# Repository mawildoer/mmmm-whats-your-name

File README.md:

# mmmm-whats-your-name

This is a simple LED matrix, with boost converters to run from a single-cell LiPo.

It's based on an RP2040 and SK6805 LEDs.

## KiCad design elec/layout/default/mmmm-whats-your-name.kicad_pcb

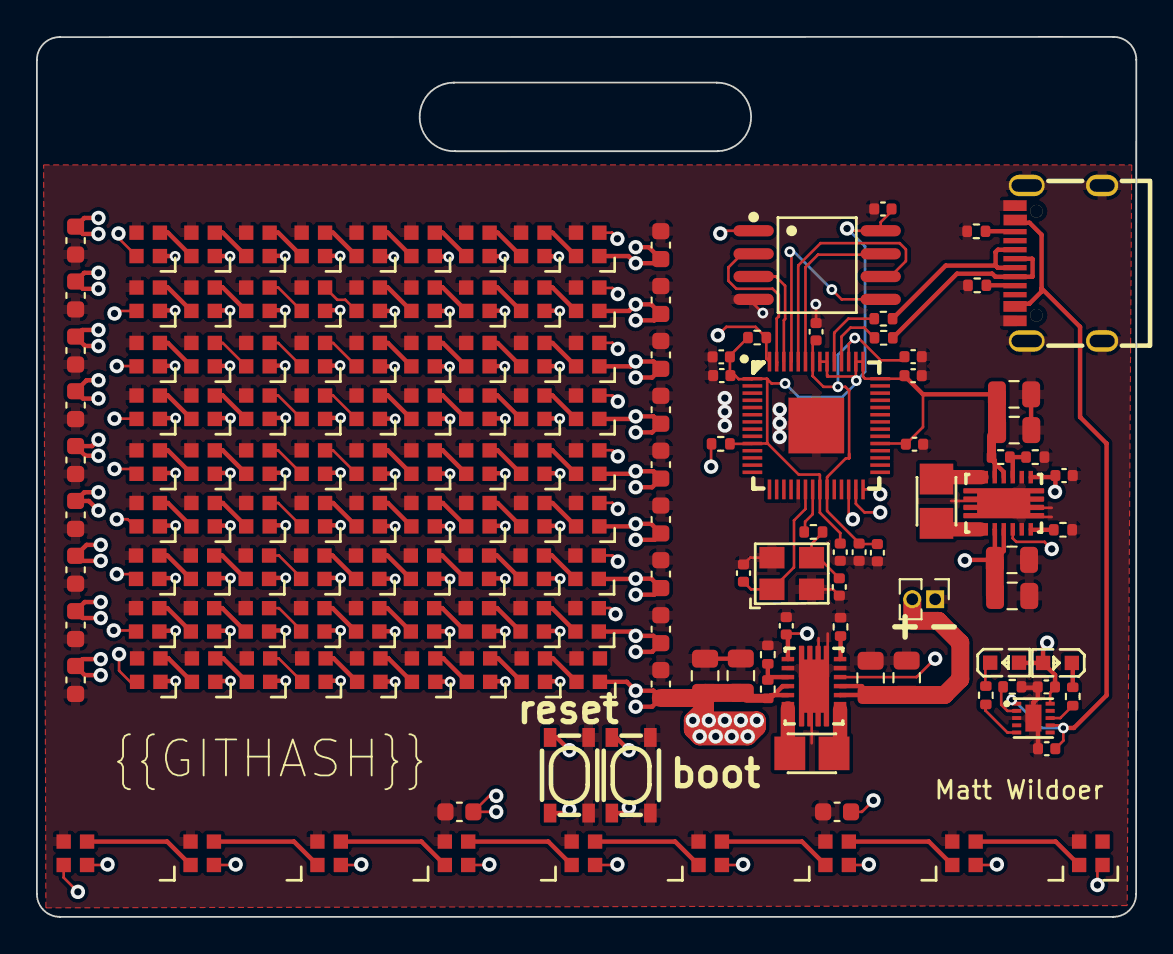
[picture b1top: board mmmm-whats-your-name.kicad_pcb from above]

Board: 4 copper layers, 61.1 x 48.9 mm, 164 parts (0 on the bottom side), 127 nets.

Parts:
C1, C2, C3, C4, C6, C7, C8, C9: Multilayer Ceramic Capacitors MLCC - SMD/SMT 10uF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; C0805
C5, C10, C15, C16, C17, C18, C19, C21, C22, C23: Multilayer Ceramic Capacitors MLCC - SMD/SMT 100n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; C0402
C11, C12, C20, C24: Multilayer Ceramic Capacitors MLCC - SMD/SMT 1uF 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; C0402
C13, C14: Multilayer Ceramic Capacitors MLCC - SMD/SMT 20pF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; C0402
C25, C26, C27, C28, C29, C30, C31, C32, C33, C34, C35, C36, C37, C38, C39, C40, C41, C42, C43, C44: Multilayer Ceramic Capacitors MLCC - SMD/SMT 2.2u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; C0603
L1, L2: IND-SMD_L2.5-W2.0_WPN252012H
LED1, LED2: LED0603-RD
R1, R3, R6: Chip Resistor - Surface Mount 1MOhms ±5% 1/16W 04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; R0402
R2, R5: Chip Resistor - Surface Mount 180KOhms ±5% 1/16W 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; R0402
R4: Chip Resistor - Surface Mount 1.6MOhms ±5% 1/16W 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; R0402
R7, R8: Chip Resistor - Surface Mount 4.7KOhms ±5% 1/16W 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; R0402
R9: Chip Resistor - Surface Mount 560Ohms ±5% 1/16W 0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; R0402
R10: Chip Resistor - Surface Mount 120Ohms ±5% 1/16W 0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; R0402
R11: Chip Resistor - Surface Mount 82Ohms ±5% 1/16W 04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; R0402
R12: Chip Resistor - Surface Mount 1KOhms ±5% 1/16W 04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; R0402
R13, R14: Chip Resistor - Surface Mount 27KOhms ±5% 1/16W 0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; R0402
R15: Chip Resistor - Surface Mount 11KOhms ±5% 1/16W 0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; R0402
R16: Chip Resistor - Surface Mount 10KOhms ±5% 1/16W 0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; R0402
U1: PinHeader_1x02_P1.27mm_Vertical
U2, U3: VSON-14_L4.0-W3.0-P0.50-BL-EP_TI_DSJ
U4: USB-C-SMD_KH-TYPE-C-16P
U5: WSON-10_L2.0-W2.0-P0.40-BL-EP
U6: LQFN-56_L7.0-W7.0-P0.4-EP
U7: OSC-SMD_4P-L3.2-W2.5-BL
U8: SOIC-8_L5.3-W5.3-P1.27-LS8.0-BL
U9, U10: KEY-SMD_4P-L4.2-W3.2-P2.20-LS4.6
U11, U12, U13, U14, U15, U16, U17, U18, U19, U20, U21, U22, U23, U24, U25, U26, U27, U28, U29, U30, U31, U32, U33, U34, U35, U36, U37, U38, U39, U40, U41, U42, U43, U44, U45, U46, U47, U48, U49, U50, U51, U52, U53, U54, U55, U56, U57, U58, U59, U60, U61, U62, U63, U64, U65, U66, U67, U68, U69, U70, U71, U72, U73, U74, U75, U76, U77, U78, U79, U80, U81, U82, U83, U84, U85, U86, U87, U88, U89, U90, U91, U92, U93, U94, U95, U96, U97, U98, U99, U100: LED-SMD_4P-L2.0-W2.0-BR

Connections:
cathode: LED1.1, R10.1
cathode-1: LED2.1, R11.1
cc1: R7.1, U4.A5
cc2: R8.1, U4.B5
cs: R16.2, U6.56, U8.1, U10.1, U10.2
dm: R14.1, U4.A7, U4.B7
dp: R13.2, U4.A6, U4.B6
gnd: C1.2, C2.2, C3.2, C4.2, C5.2, C6.2, C7.2, C8.2, C9.2, C10.2, C11.2, C12.2, C13.2, C14.2, C15.2, C16.2, C17.2, C18.2, C19.2, C20.2, C21.2, C22.2, C23.2, C24.2, C25.2, C26.2, C27.2, C28.2, C29.2, C30.2, C31.2, C32.2, C33.2, C34.2, C35.2, C36.2, C37.2, C38.2, C39.2, C40.2, C41.2, C42.2, C43.2, C44.2, R2.2, R3.2, R5.2, R6.2, R7.2, R8.2, R9.2, U1.1, U2.2, U2.13, U2.15, U3.2, U3.13, U3.15, U4.1, U4.2, U4.3, U4.4, U4.A1, U4.A12, U4.B1, U4.B12, U5.3, U5.11, U6.19, U6.57, U7.2, U7.4, U8.4, U9.3, U9.4, U10.3, U10.4, U11.3, U12.3, U13.3, U14.3, U15.3, U16.3, U17.3, U18.3, U19.3, U20.3, U21.3, U22.3, U23.3, U24.3, U25.3, U26.3, U27.3, U28.3, U29.3, U30.3, U31.3, U32.3, U33.3, U34.3, U35.3, U36.3, U37.3, U38.3, U39.3, U40.3, U41.3, U42.3, U43.3, U44.3, U45.3, U46.3, U47.3, U48.3, U49.3, U50.3, U51.3, U52.3, U53.3, U54.3, U55.3, U56.3, U57.3, U58.3, U59.3, U60.3, U61.3, U62.3, U63.3, U64.3, U65.3, U66.3, U67.3, U68.3, U69.3, U70.3, U71.3, U72.3, U73.3, U74.3, U75.3, U76.3, U77.3, U78.3, U79.3, U80.3, U81.3, U82.3, U83.3, U84.3, U85.3, U86.3, U87.3, U88.3, U89.3, U90.3, U91.3, U92.3, U93.3, U94.3, U95.3, U96.3, U97.3, U98.3, U99.3, U100.3
gnd-3: R10.2, U5.5
gnd-4: R11.2, U5.8
gpio16: U6.27, U11.4
gpio17: U6.28, U92.4
io0: U6.53, U8.5
io1: U6.55, U8.2
io2: U6.54, U8.3
io3: U6.51, U8.7
iset: R9.1, U5.2
l1: L1.1, U2.8, U2.9
l1-1: L2.1, U3.8, U3.9
l2: L1.2, U2.6, U2.7
l2-1: L2.2, U3.6, U3.7
out: R1.2, R2.1, U2.3
out-1: R4.2, R5.1, U3.3
out-2: C14.1, R12.2, U7.3
pg: R3.1, U2.14
pg-1: R6.1, U3.14
run: R15.2, U6.26, U9.1, U9.2
sck: U6.52, U8.6
usb_dm: R14.2, U6.46
usb_dp: R13.1, U6.47
vcc: C1.1, C2.1, C6.1, C7.1, C12.1, LED1.2, LED2.2, U1.2, U2.10, U2.11, U3.10, U3.11, U5.10
vcc-1: C3.1, C4.1, C15.1, C16.1, C17.1, C18.1, C19.1, C20.1, R1.1, R15.1, R16.1, U2.4, U2.5, U6.1, U6.10, U6.22, U6.33, U6.42, U6.43, U6.44, U6.48, U6.49, U8.8
vcc-2: C8.1, C9.1, C25.1, C26.1, C27.1, C28.1, C29.1, C30.1, C31.1, C32.1, C33.1, C34.1, C35.1, C36.1, C37.1, C38.1, C39.1, C40.1, C41.1, C42.1, C43.1, C44.1, R4.1, U3.4, U3.5, U11.1, U12.1, U13.1, U14.1, U15.1, U16.1, U17.1, U18.1, U19.1, U20.1, U21.1, U22.1, U23.1, U24.1, U25.1, U26.1, U27.1, U28.1, U29.1, U30.1, U31.1, U32.1, U33.1, U34.1, U35.1, U36.1, U37.1, U38.1, U39.1, U40.1, U41.1, U42.1, U43.1, U44.1, U45.1, U46.1, U47.1, U48.1, U49.1, U50.1, U51.1, U52.1, U53.1, U54.1, U55.1, U56.1, U57.1, U58.1, U59.1, U60.1, U61.1, U62.1, U63.1, U64.1, U65.1, U66.1, U67.1, U68.1, U69.1, U70.1, U71.1, U72.1, U73.1, U74.1, U75.1, U76.1, U77.1, U78.1, U79.1, U80.1, U81.1, U82.1, U83.1, U84.1, U85.1, U86.1, U87.1, U88.1, U89.1, U90.1, U91.1, U92.1, U93.1, U94.1, U95.1, U96.1, U97.1, U98.1, U99.1, U100.1
vcc-3: C11.1, U4.A4, U4.A9, U4.B4, U4.B9, U5.1, U5.7
vcc-6: C21.1, C22.1, C23.1, C24.1, U6.23, U6.45, U6.50
vcc-8: U19.2, U20.4
vcc-9: U11.2, U12.4
vcc-10: U12.2, U13.4
vcc-11: U13.2, U14.4
vcc-12: U14.2, U15.4
vcc-13: U15.2, U16.4
vcc-14: U16.2, U17.4
vcc-15: U17.2, U18.4
vcc-16: U18.2, U19.4
vcc-17: U28.2, U29.4
vcc-18: U20.2, U21.4
vcc-19: U21.2, U22.4
vcc-20: U22.2, U23.4
vcc-21: U23.2, U24.4
vcc-22: U24.2, U25.4
vcc-23: U25.2, U26.4
vcc-24: U26.2, U27.4
vcc-25: U27.2, U28.4
vcc-26: U37.2, U38.4
vcc-27: U29.2, U30.4
vcc-28: U30.2, U31.4
vcc-29: U31.2, U32.4
vcc-30: U32.2, U33.4
vcc-31: U33.2, U34.4
vcc-32: U34.2, U35.4
vcc-33: U35.2, U36.4
vcc-34: U36.2, U37.4
vcc-35: U46.2, U47.4
vcc-36: U38.2, U39.4
vcc-37: U39.2, U40.4
vcc-38: U40.2, U41.4
vcc-39: U41.2, U42.4
vcc-40: U42.2, U43.4
vcc-41: U43.2, U44.4
vcc-42: U44.2, U45.4
vcc-43: U45.2, U46.4
vcc-44: U55.2, U56.4
vcc-45: U47.2, U48.4
vcc-46: U48.2, U49.4
vcc-47: U49.2, U50.4
vcc-48: U50.2, U51.4
vcc-49: U51.2, U52.4
vcc-50: U52.2, U53.4
vcc-51: U53.2, U54.4
vcc-52: U54.2, U55.4
vcc-53: U64.2, U65.4
vcc-54: U56.2, U57.4
vcc-55: U57.2, U58.4
vcc-56: U58.2, U59.4
vcc-57: U59.2, U60.4
vcc-58: U60.2, U61.4
vcc-59: U61.2, U62.4
vcc-60: U62.2, U63.4
vcc-61: U63.2, U64.4
vcc-62: U73.2, U74.4
vcc-63: U65.2, U66.4
vcc-64: U66.2, U67.4
vcc-65: U67.2, U68.4
vcc-66: U68.2, U69.4
vcc-67: U69.2, U70.4
vcc-68: U70.2, U71.4
vcc-69: U71.2, U72.4
vcc-70: U72.2, U73.4
vcc-71: U82.2, U83.4
vcc-72: U74.2, U75.4
vcc-73: U75.2, U76.4
vcc-74: U76.2, U77.4
vcc-75: U77.2, U78.4
vcc-76: U78.2, U79.4
vcc-77: U79.2, U80.4
vcc-78: U80.2, U81.4
vcc-79: U81.2, U82.4
vcc-80: U83.2, U84.4
vcc-81: U84.2, U85.4
vcc-82: U85.2, U86.4
vcc-83: U86.2, U87.4
vcc-84: U87.2, U88.4
vcc-85: U88.2, U89.4
vcc-86: U89.2, U90.4
vcc-87: U90.2, U91.4
vcc-89: U92.2, U93.4
vcc-90: U93.2, U94.4
vcc-91: U94.2, U95.4
vcc-92: U95.2, U96.4
vcc-93: U96.2, U97.4
vcc-94: U97.2, U98.4
vcc-95: U98.2, U99.4
vcc-96: U99.2, U100.4
vina: C5.1, U2.1, U2.12
vina-1: C10.1, U3.1, U3.12
xin: C13.1, U6.20, U7.1
xout: R12.1, U6.21

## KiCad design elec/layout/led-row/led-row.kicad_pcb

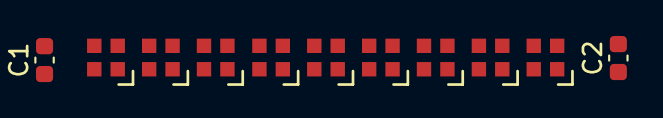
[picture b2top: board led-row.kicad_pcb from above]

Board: 2 copper layers, 11 parts (0 on the bottom side), 10 nets, no tracks yet.

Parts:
C1, C2: Multilayer Ceramic Capacitors MLCC - SMD/SMT 2.2u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; C0603
U1, U2, U3, U4, U5, U6, U7, U8, U9: LED-SMD_4P-L2.0-W2.0-BR

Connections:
gnd: C1.2, C2.2, U1.3, U2.3, U3.3, U4.3, U5.3, U6.3, U7.3, U8.3, U9.3
vcc: C1.1, C2.1, U1.1, U2.1, U3.1, U4.1, U5.1, U6.1, U7.1, U8.1, U9.1
vcc-3: U1.2, U2.4
vcc-4: U2.2, U3.4
vcc-5: U3.2, U4.4
vcc-6: U4.2, U5.4
vcc-7: U5.2, U6.4
vcc-8: U6.2, U7.4
vcc-9: U7.2, U8.4
vcc-10: U8.2, U9.4

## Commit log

2024-02-25 Configure project
2024-02-25 Build works, but there's too many LEDs
2024-02-25 Rough blocks are in the right places
2024-02-25 Placement done!
2024-02-25 Layout's done!
2024-02-25 Add reset/boot buttons
2024-02-25 This commit does a couple of semi-questionable things: 1. I add two footprints/modules directly to the repo I don't think I need 2. I ungrouped everything (which screws up the sync to the other layou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
2024-02-25 Nice edges
2024-02-25 Add graphics to README
2024-03-25 Add firwmare
